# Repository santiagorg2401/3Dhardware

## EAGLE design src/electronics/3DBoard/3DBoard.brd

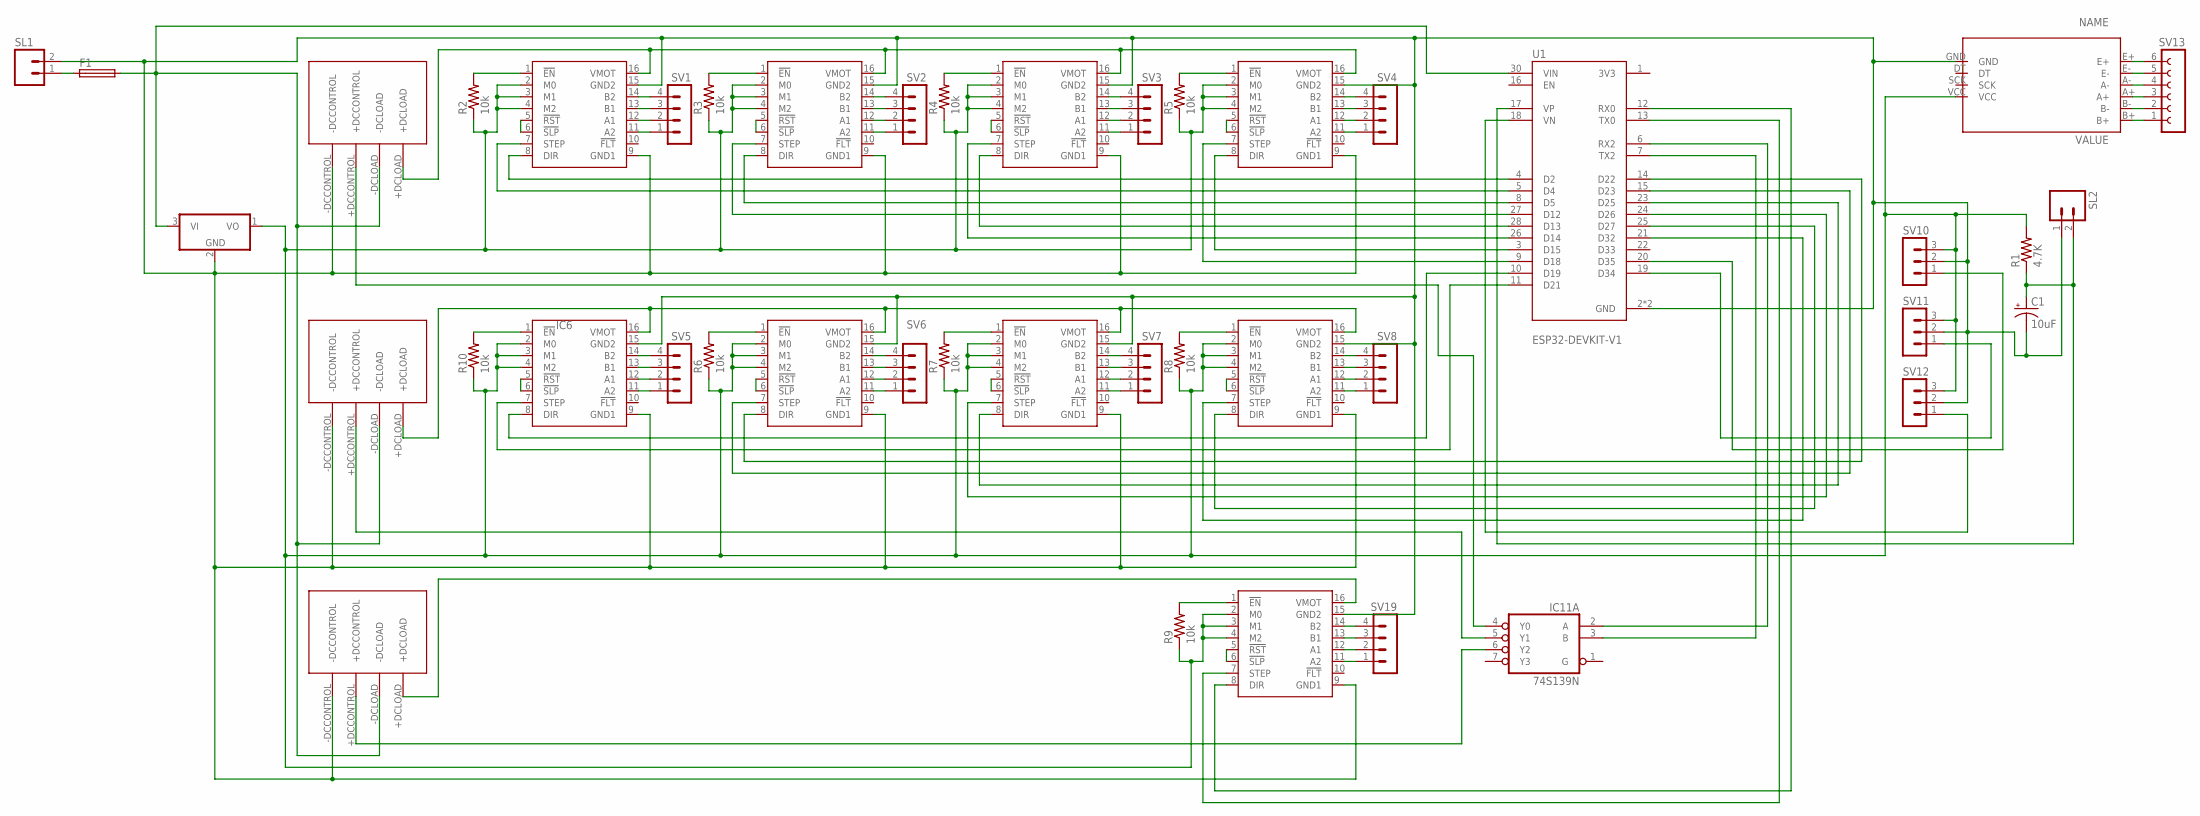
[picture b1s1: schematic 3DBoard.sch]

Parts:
C1: 10uF; B45181B
F1: GSH15
IC1: 78L05Z; TO92
IC2, IC3, IC4, IC5, IC6, IC7, IC8, IC9, IC10: 2987-DRV8825; DRV8825
IC11: 74S139N; DIL16
R1: 4.7K; 0204/7
R2, R3, R4, R5, R6, R7, R8, R9, R10: 10k; 0204/7
SL1, SL2: M02; 02P
SV1, SV2, SV3, SV4, SV5, SV6, SV7, SV8, SV19: MA04-1
SV10, SV11, SV12: MA03-1
SV13: FE06-1; FE06
U1: ESP32-DEVKIT-V1; MODULE_ESP32_DEVKIT_V1
U$2: HX711A; HX711
U$3, U$4, U$5: CMX60D10; SIP-4

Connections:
GND: IC11.8 (GND)
unnamed: IC2.8 (DIR), U1.4 (D2)
unnamed: IC10.16 (VMOT), U$5.+DCLOAD
unnamed: IC6.16 (VMOT), IC7.16 (VMOT), IC8.16 (VMOT), IC9.16 (VMOT), U$4.+DCLOAD
unnamed: IC2.16 (VMOT), IC3.16 (VMOT), IC4.16 (VMOT), IC5.16 (VMOT), U$3.+DCLOAD
unnamed: IC5.11 (A2), SV4.1
unnamed: IC2.7 (STEP), U1.5 (D4)
unnamed: IC5.12 (A1), SV4.2
unnamed: IC5.13 (B1), SV4.3
unnamed: IC5.14 (B2), SV4.4
unnamed: IC9.11 (A2), SV8.1
unnamed: IC9.12 (A1), SV8.2
unnamed: IC9.13 (B1), SV8.3
unnamed: IC9.14 (B2), SV8.4
unnamed: IC10.11 (A2), SV19.1
unnamed: IC10.12 (A1), SV19.2
unnamed: IC10.13 (B1), SV19.3
unnamed: IC10.14 (B2), SV19.4
unnamed: IC4.11 (A2), SV3.1
unnamed: IC4.12 (A1), SV3.2
unnamed: IC4.13 (B1), SV3.3
unnamed: IC4.14 (B2), SV3.4
unnamed: IC3.11 (A2), SV2.1
unnamed: IC3.12 (A1), SV2.2
unnamed: IC3.13 (B1), SV2.3
unnamed: IC3.14 (B2), SV2.4
unnamed: IC2.11 (A2), SV1.1
unnamed: IC2.12 (A1), SV1.2
unnamed: IC2.13 (B1), SV1.3
unnamed: IC2.14 (B2), SV1.4
unnamed: IC6.11 (A2), SV5.1
unnamed: IC6.12 (A1), SV5.2
unnamed: IC6.13 (B1), SV5.3
unnamed: IC6.14 (B2), SV5.4
unnamed: IC7.11 (A2), SV6.1
unnamed: IC7.12 (A1), SV6.2
unnamed: IC7.13 (B1), SV6.3
unnamed: SV13.1, U$2.B+
unnamed: SV13.2, U$2.B-
unnamed: SV13.3, U$2.A+
unnamed: SV13.4, U$2.A-
unnamed: SV13.5, U$2.E-
unnamed: SV13.6, U$2.E+
unnamed: C1.-, IC1.2 (GND), IC2.9 (GND1), IC2.15 (GND2), IC3.9 (GND1), IC3.15 (GND2), IC4.9 (GND1), IC4.15 (GND2), IC5.9 (GND1), IC5.15 (GND2), IC6.9 (GND1), IC6.15 (GND2), IC7.9 (GND1), IC7.15 (GND2), IC8.9 (GND1), IC8.15 (GND2), IC9.9 (GND1), IC9.15 (GND2), IC10.9 (GND1), IC10.15 (GND2), SL1.2, SL2.1, SV10.2, SV11.2, SV12.2, U1.2 (GND), U1.29 (GND), U$2.GND, U$3.-DCCONTROL, U$4.-DCCONTROL, U$5.-DCCONTROL
unnamed: IC7.14 (B2), SV6.4
unnamed: IC8.11 (A2), SV7.1
unnamed: F1.1, SL1.1
unnamed: IC8.12 (A1), SV7.2
unnamed: IC8.13 (B1), SV7.3
unnamed: IC8.14 (B2), SV7.4
unnamed: IC3.8 (DIR), U1.8 (D5)
unnamed: IC3.7 (STEP), U1.27 (D12)
unnamed: IC4.8 (DIR), U1.28 (D13)
unnamed: IC4.7 (STEP), U1.26 (D14)
unnamed: IC5.8 (DIR), U1.3 (D15)
unnamed: IC2.5 (!RST), IC2.6 (!SLP)
unnamed: IC3.5 (!RST), IC3.6 (!SLP)
unnamed: IC4.5 (!RST), IC4.6 (!SLP)
unnamed: IC5.5 (!RST), IC5.6 (!SLP)
unnamed: IC6.5 (!RST), IC6.6 (!SLP)
unnamed: IC7.5 (!RST), IC7.6 (!SLP)
unnamed: IC8.5 (!RST), IC8.6 (!SLP)
unnamed: IC9.5 (!RST), IC9.6 (!SLP)
unnamed: IC10.5 (!RST), IC10.6 (!SLP)
unnamed: IC2.1 (!EN), R2.2
unnamed: IC3.1 (!EN), R3.2
unnamed: IC4.1 (!EN), R4.2
unnamed: IC5.1 (!EN), R5.2
unnamed: IC7.1 (!EN), R6.2
unnamed: IC8.1 (!EN), R7.2
unnamed: IC9.1 (!EN), R8.2
unnamed: IC10.1 (!EN), R9.2
unnamed: IC6.1 (!EN), R10.2
unnamed: IC5.7 (STEP), U1.9 (D18)
unnamed: IC6.8 (DIR), U1.10 (D19)
unnamed: F1.2, IC1.3 (VI), U1.30 (VIN), U$3.-DCLOAD, U$4.-DCLOAD, U$5.-DCLOAD
unnamed: IC1.1 (VO), IC2.2 (M0), IC2.3 (M1), IC2.4 (M2), IC3.2 (M0), IC3.3 (M1), IC3.4 (M2), IC4.2 (M0), IC4.3 (M1), IC4.4 (M2), IC5.2 (M0), IC5.3 (M1), IC5.4 (M2), IC6.2 (M0), IC6.3 (M1), IC6.4 (M2), IC7.2 (M0), IC7.3 (M1), IC7.4 (M2), IC8.2 (M0), IC8.3 (M1), IC8.4 (M2), IC9.2 (M0), IC9.3 (M1), IC9.4 (M2), IC10.2 (M0), IC10.3 (M1), IC10.4 (M2), R1.2, R2.1, R3.1, R4.1, R5.1, R6.1, R7.1, R8.1, R9.1, R10.1, SV10.3, SV11.3, SV12.3, U$2.VCC
unnamed: IC6.7 (STEP), U1.11 (D21)
unnamed: IC7.8 (DIR), U1.14 (D22)
unnamed: IC7.7 (STEP), U1.15 (D23)
unnamed: IC8.8 (DIR), U1.23 (D25)
unnamed: IC8.7 (STEP), U1.24 (D26)
unnamed: IC9.8 (DIR), U1.25 (D27)
unnamed: IC9.7 (STEP), U1.21 (D32)
unnamed: IC11.6 (Y2), U$5.+DCCONTROL
unnamed: IC10.7 (STEP), U1.13 (TX0)
unnamed: IC11.4 (Y0), U$3.+DCCONTROL
unnamed: IC11.5 (Y1), U$4.+DCCONTROL
unnamed: SV10.1, U1.20 (D35)
unnamed: SV11.1, U1.19 (D34)
unnamed: IC10.8 (DIR), U1.12 (RX0)
unnamed: C1.+, R1.1, SL2.2, U1.17 (VP)
unnamed: IC11.2 (A), U1.6 (RX2)
unnamed: IC11.3 (B), U1.7 (TX2)
unnamed: SV12.1, U1.18 (VN)
VCC: IC11.16 (VCC)

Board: 2 copper layers, 43 parts (0 on the bottom side), 94 nets, no tracks yet.

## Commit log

2022-05-28 Initial commit.
2022-05-29 First 3DBoard commit.
2022-05-29 Back up files deleted.
2022-05-29 Wiring added and schematics are cleaner.
